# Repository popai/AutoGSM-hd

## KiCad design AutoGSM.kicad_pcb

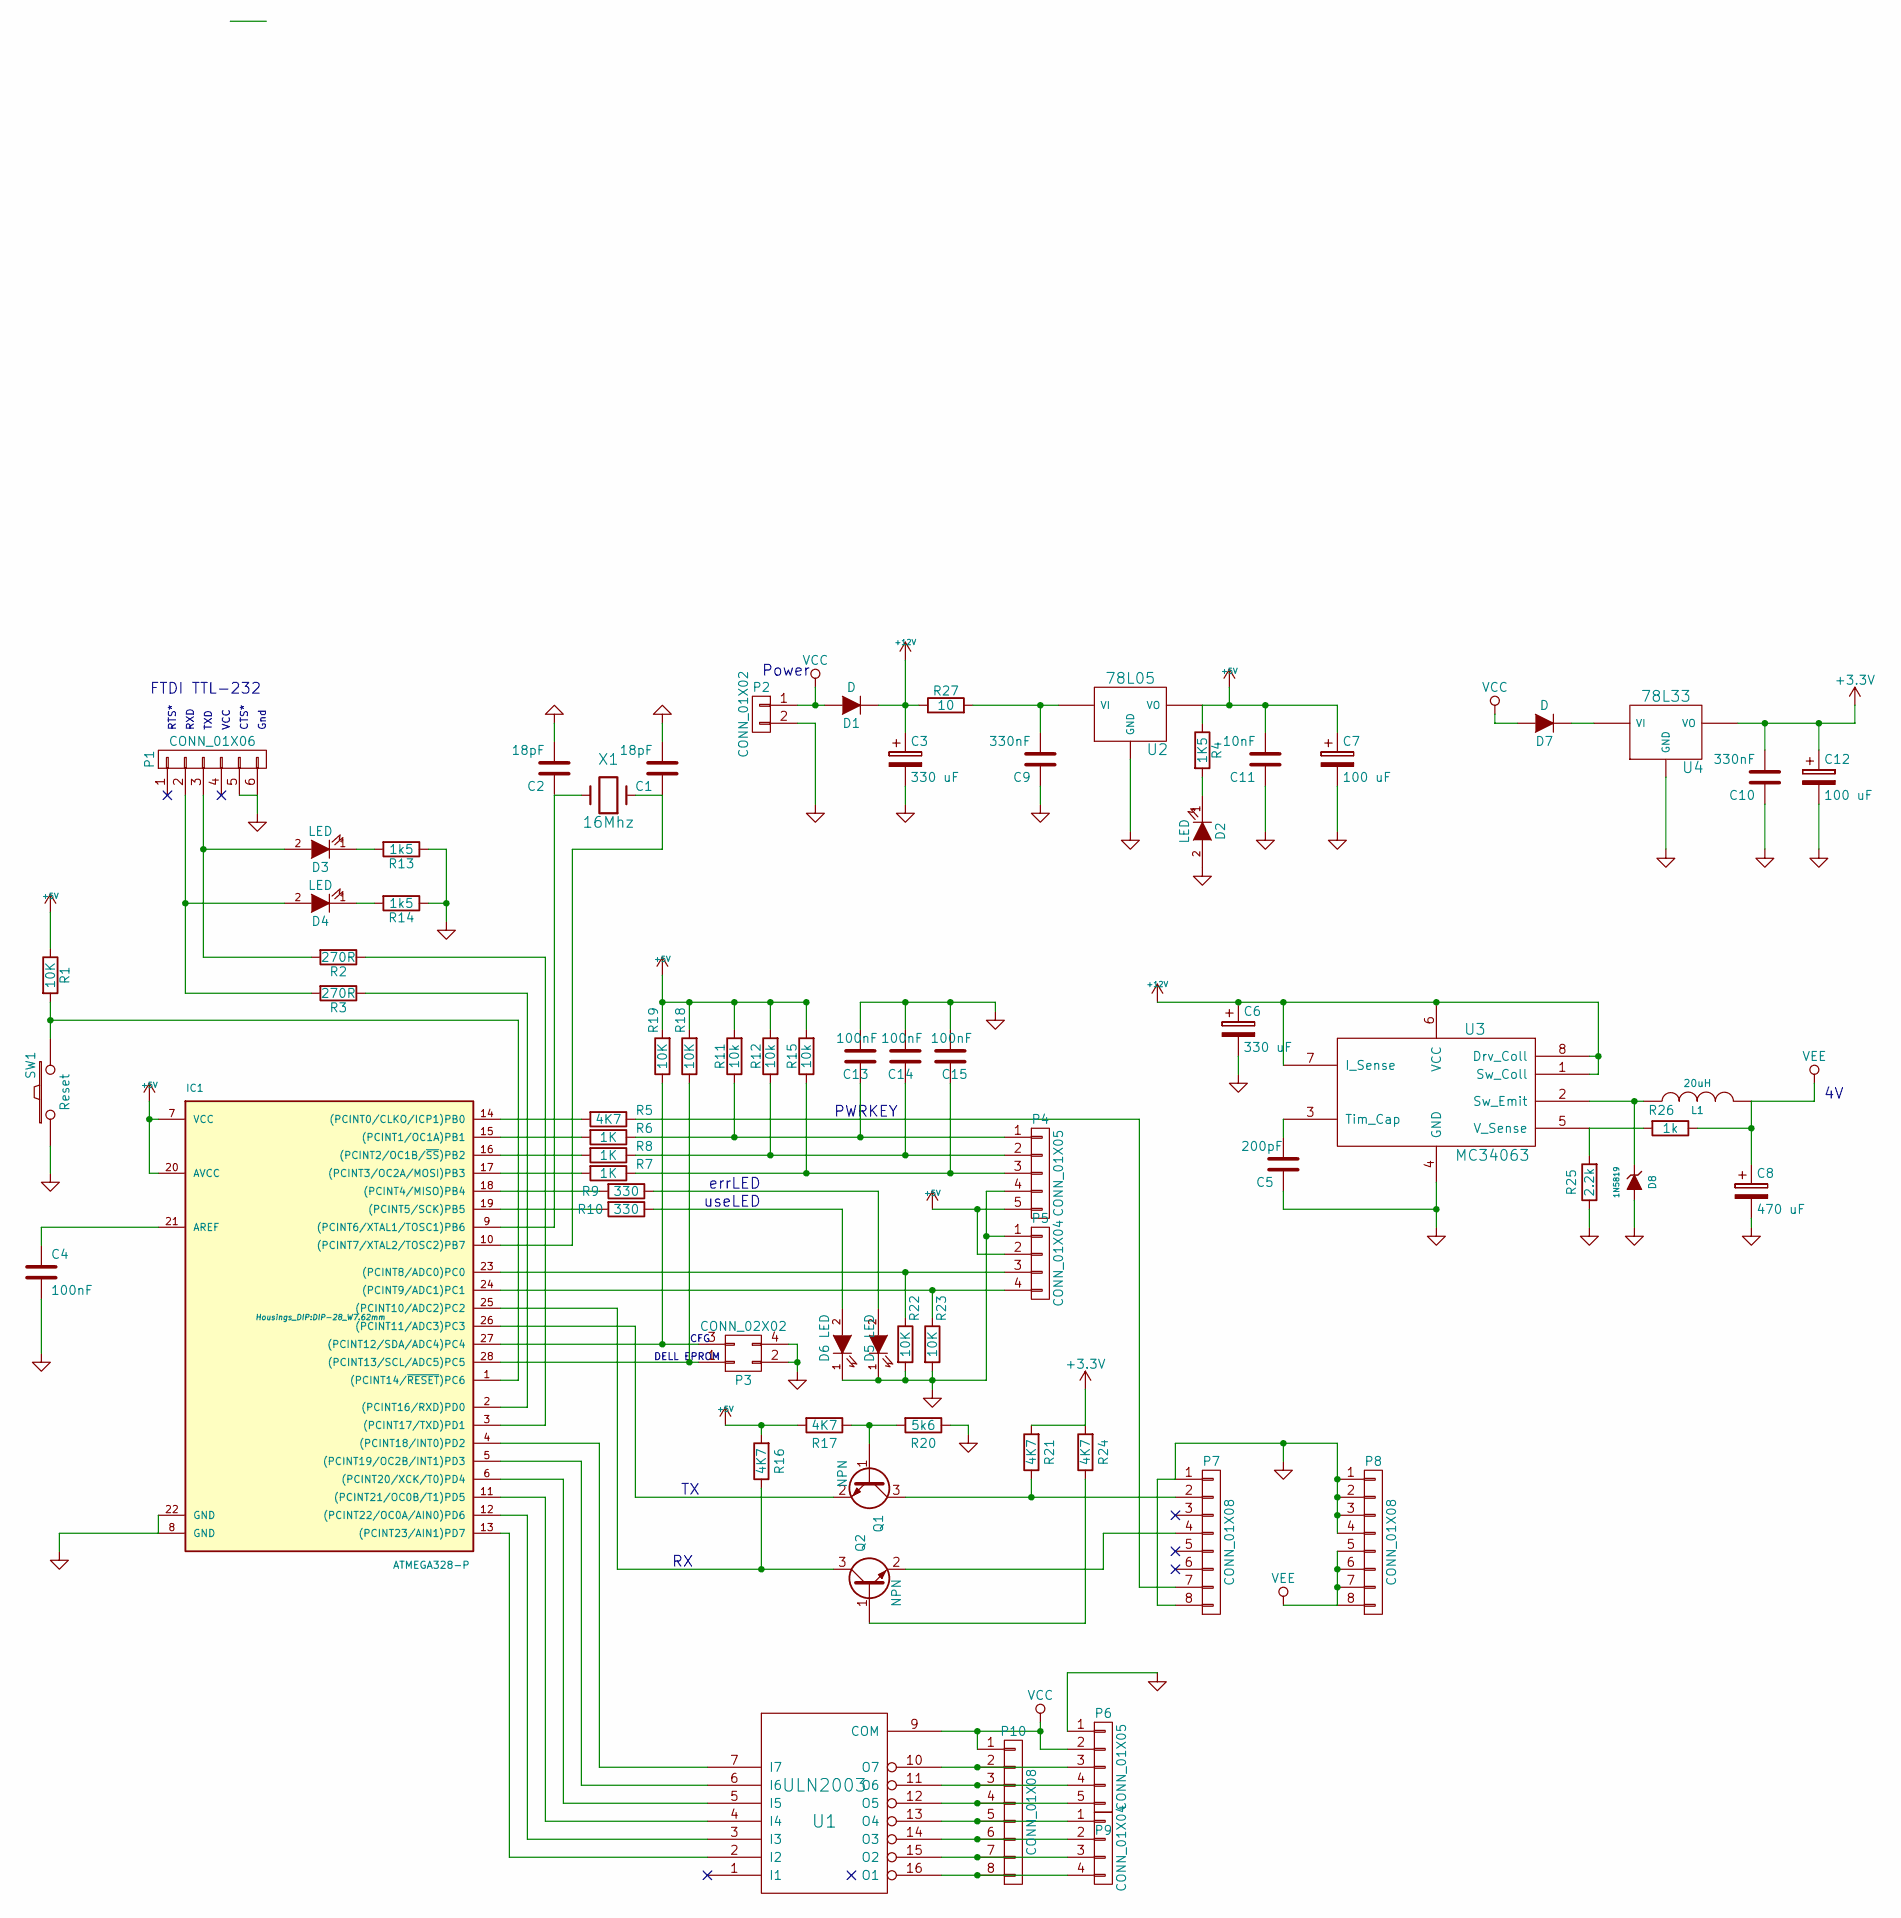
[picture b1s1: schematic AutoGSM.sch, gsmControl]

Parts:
C1, C2: 18pF; C_Disc_D3_P2.5
C3, C6: 330 uF; C_Radial_D5_L6_P2.5
C4, C13, C14, C15: 100nF; C_Rect_L7_W2_P5
C5: 200pF; C_Rect_L7_W2_P5
C7, C12: 100 uF; C_Radial_D5_L6_P2.5
C8: 470 uF; C_Radial_D7.5_L11.2_P2.5
C9, C10: 330nF; C_Rect_L7_W2_P5
C11: 10nF; C_Rect_L7_W2_P5
D1, D7: D; Diode_DO-35_SOD27_Horizontal_RM10
D2, D3, D4, D5, D6: LED; LED-3MM
D8: 1N5819; Diode_DO-35_SOD27_Horizontal_RM10
IC1: ATMEGA328-P; DIP-28_W7.62mm
L1: 20uH; Neosid_Inductor_Sd8
P1: CONN_01X06; Pin_Header_Straight_1x06
P2: CONN_01X02; Socket_MOLEX-KK-RM3-96mm_Lock_2pin_straight
P3: CONN_02X02; Pin_Header_Straight_2x02
P4, P6: CONN_01X05; Socket_MOLEX-KK-RM3-96mm_Lock_5pin_straight
P5, P9: CONN_01X04; Socket_MOLEX-KK-RM3-96mm_Lock_4pin_straight
P7, P8, P10: CONN_01X08; Socket_Strip_Straight_1x08
Q1, Q2: NPN; TO-92_Molded_Narrow_Oval
R1, R18, R19, R22, R23: 10K; R4
R2, R3: 270R; R4
R4: 1K5; R4
R5, R16, R17, R21, R24: 4K7; R4
R6, R7, R8: 1K; R4
R9, R10: 330; R4
R11, R12, R15: 10k; R4
R13, R14: 1k5; R4
R20: 5k6; R4
R25: 2.2k; R4
R26: 1k; R4
R27: 10; R4-5
SW1: Reset; SW_PUSH_SMALL
U1: ULN2003; DIP-16_W7.62mm
U2: 78L05; TO-220_Neutral123_Vertical_LargePads
U3: MC34063; DIP-8_W7.62mm
U4: 78L33; TO-92_Inline_Wide
X1: 16Mhz; Crystal_HC49-U_Vertical

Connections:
+3V3: C10.2, C12.1, R21.2, R24.2, U4.VO
+5V: C7.1, C11.2, IC1.7 (VCC), IC1.20 (AVCC), P4.5, P5.2, R1.1, R4.1, R11.2, R12.2, R15.2, R16.2, R17.2, R18.2, R19.2, U2.VO
+12V: C3.1, C6.1, D1.1 (K), R27.1, U3.1 (Sw_Coll), U3.6 (VCC), U3.7 (I_Sense), U3.8 (Drv_Coll)
GND: C1.2, C2.2, C3.2, C4.2, C5.1, C6.2, C7.2, C8.2, C9.1, C10.1, C11.1, C12.2, C13.2, C14.2, C15.2, D2.2 (A), D5.1 (K), D6.1 (K), D8.2 (A), IC1.8 (GND), IC1.22 (GND), P1.5, P1.6, P2.2, P3.2, P3.4, P4.4, P5.1, P6.1, P7.1, P7.8, P8.1, P8.2, P8.3, P8.4, R13.1, R14.1, R20.1, R22.2, R23.2, R25.1, SW1.1, U1.8 (GND), U2.GND, U3.4 (GND), U4.GND
unnamed: C1.1, IC1.10 ((PCINT7/XTAL2/TOSC2)PB7), X1.1
unnamed: C2.1, IC1.9 ((PCINT6/XTAL1/TOSC1)PB6), X1.2
unnamed: C4.1, IC1.21 (AREF)
unnamed: C5.2, U3.3 (Tim_Cap)
unnamed: C9.2, R27.2, U2.VI
unnamed: C13.1, P4.1, R6.1, R11.1
unnamed: C14.1, P4.2, R8.1, R12.1
unnamed: C15.1, P4.3, R7.1, R15.1
unnamed: D2.1 (K), R4.2
unnamed: D3.1 (K), R13.2
unnamed: D3.2 (A), P1.3, R2.2
unnamed: D4.1 (K), R14.2
unnamed: D4.2 (A), P1.2, R3.2
unnamed: D5.2 (A), R9.1
unnamed: D6.2 (A), R10.1
unnamed: D7.1 (K), U4.VI
unnamed: D8.1 (K), L1.1, U3.2 (Sw_Emit)
unnamed: IC1.1 ((PCINT14/~RESET~)PC6), R1.2, SW1.2
unnamed: IC1.2 ((PCINT16/RXD)PD0), R3.1
unnamed: IC1.3 ((PCINT17/TXD)PD1), R2.1
unnamed: IC1.4 ((PCINT18/INT0)PD2), U1.7 (I7)
unnamed: IC1.5 ((PCINT19/OC2B/INT1)PD3), U1.6 (I6)
unnamed: IC1.6 ((PCINT20/XCK/T0)PD4), U1.5 (I5)
unnamed: IC1.11 ((PCINT21/OC0B/T1)PD5), U1.4 (I4)
unnamed: IC1.12 ((PCINT22/OC0A/AIN0)PD6), U1.3 (I3)
unnamed: IC1.13 ((PCINT23/AIN1)PD7), U1.2 (I2)
unnamed: IC1.14 ((PCINT0/CLKO/ICP1)PB0), R5.2
unnamed: IC1.15 ((PCINT1/OC1A)PB1), R6.2
unnamed: IC1.16 ((PCINT2/OC1B/~SS~)PB2), R8.2
unnamed: IC1.17 ((PCINT3/OC2A/MOSI)PB3), R7.2
unnamed: IC1.18 ((PCINT4/MISO)PB4), R9.2
unnamed: IC1.19 ((PCINT5/SCK)PB5), R10.2
unnamed: IC1.23 ((PCINT8/ADC0)PC0), P5.3, R22.1
unnamed: IC1.24 ((PCINT9/ADC1)PC1), P5.4, R23.1
unnamed: IC1.25 ((PCINT10/ADC2)PC2), Q2.3 (C), R16.1
unnamed: IC1.26 ((PCINT11/ADC3)PC3), Q1.2 (E)
unnamed: IC1.27 ((PCINT12/SDA/ADC4)PC4), P3.3, R19.1
unnamed: IC1.28 ((PCINT13/SCL/ADC5)PC5), P3.1, R18.1
unnamed: P7.2, Q1.3 (C), R21.1
unnamed: P7.4, Q2.2 (E)
unnamed: P7.7, R5.1
unnamed: P6.3, P10.2, U1.10 (O7)
unnamed: P6.4, P10.3, U1.11 (O6)
unnamed: P6.5, P10.4, U1.12 (O5)
unnamed: P9.1, P10.5, U1.13 (O4)
unnamed: P9.2, P10.6, U1.14 (O3)
unnamed: P9.3, P10.7, U1.15 (O2)
unnamed: P9.4, P10.8, U1.16 (O1)
unnamed: Q1.1 (B), R17.1, R20.2
unnamed: Q2.1 (B), R24.1
unnamed: R25.2, R26.2, U3.5 (V_Sense)
VCC: D1.2 (A), D7.2 (A), P2.1, P6.2, P10.1, U1.9 (COM)
VEE: C8.1, L1.2, P8.5, P8.6, P8.7, P8.8, R26.1

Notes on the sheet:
errLED
useLED
Power
Gnd
CTS*
VCC
TXD
RXD
RTS*
FTDI TTL-232
DELL EPROM
CFG
PWRKEY

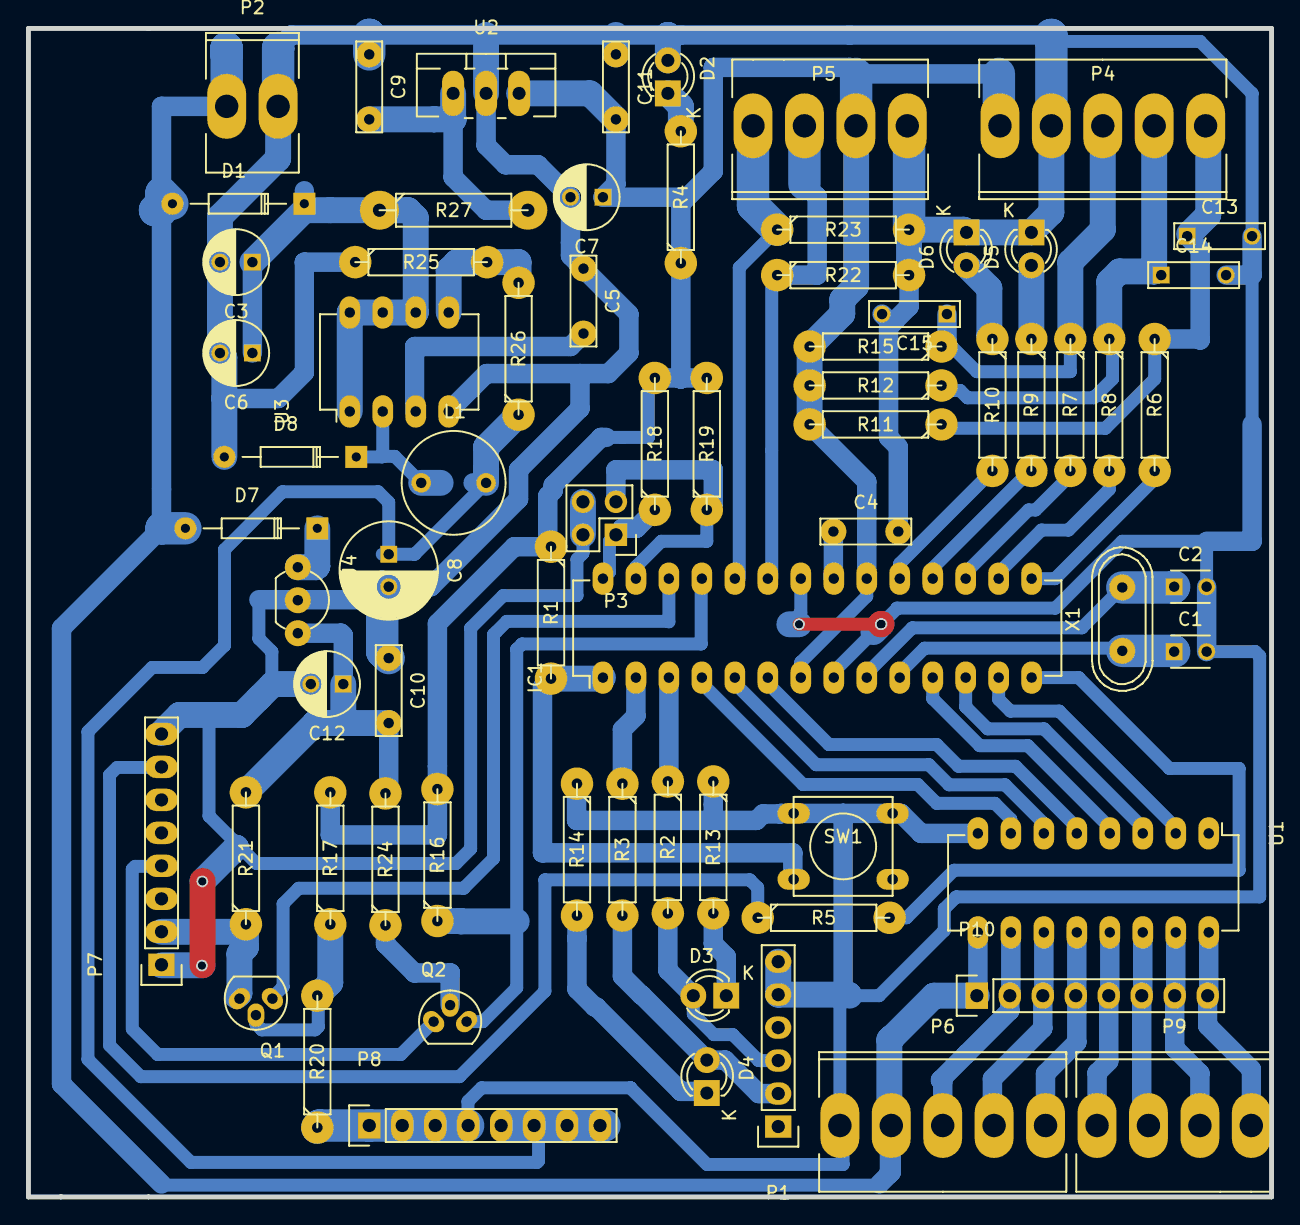
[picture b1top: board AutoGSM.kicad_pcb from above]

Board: 2 copper layers, 95.8 x 90.0 mm, 70 parts (0 on the bottom side), 57 nets.

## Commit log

2016-03-14 sim300 commander
    commander cu modul sim300
